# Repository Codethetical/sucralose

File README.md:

# Sucralose

Sucralose is a wireless, 50-key split keyboard built around Kailh PG1316S ultra-low-profile switches.
One reversible PCB serves both halves.

## Rev. 2

Rev. 2 keeps the Rev. 1 key layout and adds:

- **A 7th column on both halves:** four Kailh PG1316M switches sit on a strip outboard of the pinky column.
  Their narrow keycaps, mounted in portrait, minimize the added width.
  The strip is a breakaway section, so you can snap it off and keep a 42-key board.
- **A larger battery cutout:** the bigger opening in the PCB allows a slimmer battery cover.
- **Pads for a slide switch and reset button:** both are on the board edge.

The two halves stacked are now under 13.5 mm tall.

## Hardware

- **Switches:** [Kailh PG1316S](https://www.kailhswitch.com/uploads/15927/files/CPG1316S01D02-data-sheet.pdf),
  21 per half, on a 17 mm pitch to fit their smaller keycaps.
- **7th column:** Kailh PG1316M, 4 per half, on the breakaway strip. The firmware runs with or without it.
- **Controller:** Seeed XIAO nRF52840 Plus, running [ZMK](https://zmk.dev).
- **Display:** [nice!view](https://nicekeyboards.com/nice-view/), soldered flush to keep the stack low.
- **Power:** a LiPo pouch in a corner cutout beside the key field, a JST-PH connector, and a side slide switch.
  An optional side reset button is also supported.
- **PCB:** 1 mm thick, so the full stack stays in ultra-low-profile range.

## Design

- **Layout:** the column splay is inspired by [chalk](https://github.com/maurzo/chalk).
  The 1.5u outer thumb key comes from the [Corne](https://github.com/foostan/crkbd).
- **Reversible:** each half uses the same board, flipped.
  - The XIAO footprint puts a land on both copper layers at every pin.
    Each layer carries the net that pin needs when the module is mounted on that side.
  - The nice!view header can't do that because its pins are plated through-holes.
    Four solder jumpers per side select its pin order instead.
- **Serviceable switches:** the PG1316S contacts sit under the switch body.
  The custom footprint uses plated through-holes so each joint can be reflowed from the underside.

## Custom Footprints

These live in `lib/footprints.pretty/`. The files ending in `_sucralose` were drawn for this board.

- **PG1316S:** a reversible footprint with plated through-holes and locating-pin holes.
  It builds on [mikefive](https://github.com/mikeholscher/zmk-config-mikefive)'s footprints and
  [marbastlib](https://github.com/ebastler/marbastlib)'s.
- **PG1316M:** a reversible footprint with plated through-hole terminals, derived from
  [libmodulo](https://github.com/dennisleexyz/libmodulo)'s.
- **XIAO nRF52840 Plus:** a reversible version of Seeed's official single-sided footprint.
- **nice!view:** a dual-sided header, plus chevron solder jumpers for net selection.
- **Alps SSSS811101 power switch:** front and back versions, checked against
  [ceoloide's footprints](https://github.com/ceoloide/ergogen-footprints).
- **Other parts:** a reversible B3U reset button and SOD-123 diodes.

## Case

`case/out/` has STL files for the partial covers: a battery cover and battery plate, left and right XIAO covers, and a screen cover.
It also has left and right reference DXFs showing the outline, keycap clearances, and M1 screw holes.

## Firmware

This repo is also the [ZMK module](https://zmk.dev/docs/features/modules) for the board: `firmware/` holds the
`sucralose_left` / `sucralose_right` shield. See [`firmware/README.md`](firmware/README.md) for how to build it.

## License

Sucralose is released under the [MIT License](LICENSE).

The key switch layout is the exception. To the extent it is unchanged from [chalk](https://github.com/maurzo/chalk) by maurzo,
that layout stays under chalk's [CC BY-NC-SA 4.0](https://creativecommons.org/licenses/by-nc-sa/4.0/) license.
Third-party files in `reference/` and the footprints derived from upstream libraries also keep their own licenses.

## Credits

- **Corne:** [foostan/crkbd](https://github.com/foostan/crkbd), CC-BY-4.0.
- **Key switch layout:** [maurzo/chalk](https://github.com/maurzo/chalk) by maurzo, CC-BY-NC-SA-4.0.
- **PG1316S footprints:** [mikeholscher/zmk-config-mikefive](https://github.com/mikeholscher/zmk-config-mikefive)
  and [ebastler/marbastlib](https://github.com/ebastler/marbastlib), CERN-OHL-P.
- **PG1316M footprint and 3D model:** [dennisleexyz/libmodulo](https://github.com/dennisleexyz/libmodulo), GPL-3.0.

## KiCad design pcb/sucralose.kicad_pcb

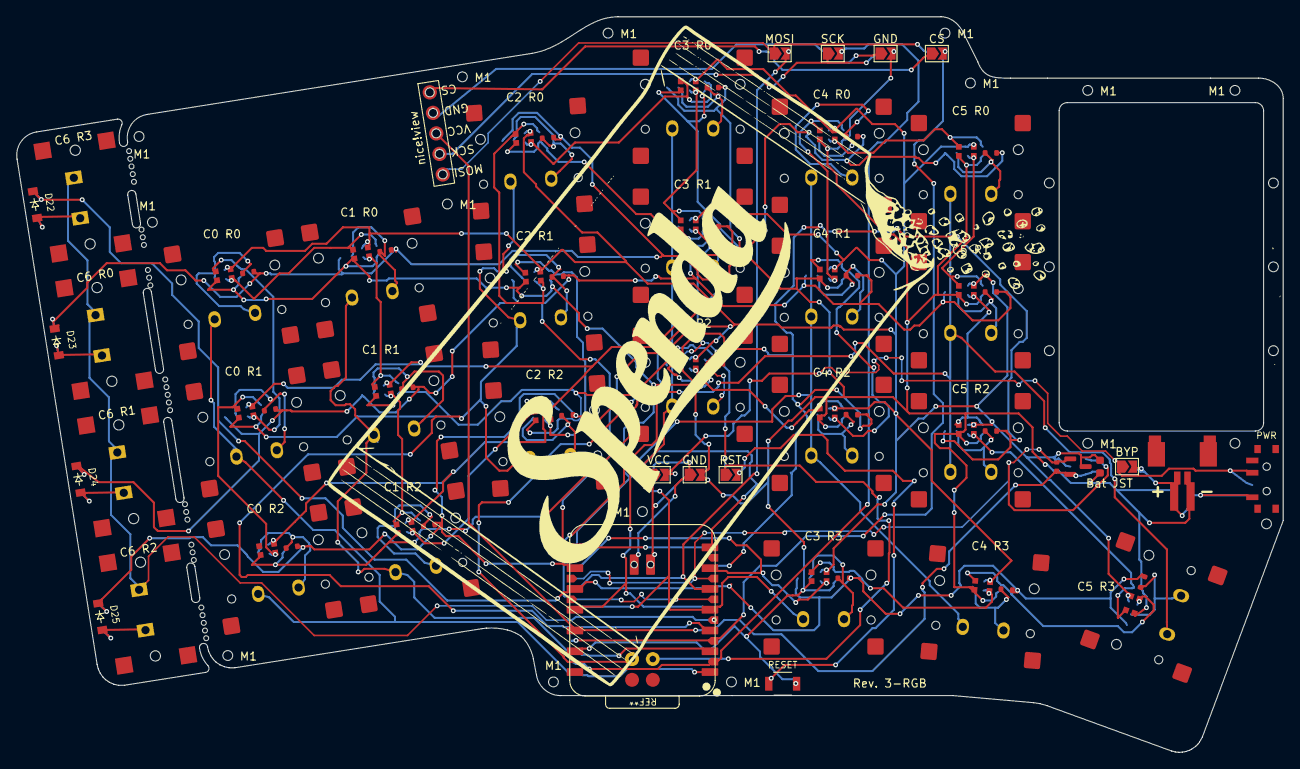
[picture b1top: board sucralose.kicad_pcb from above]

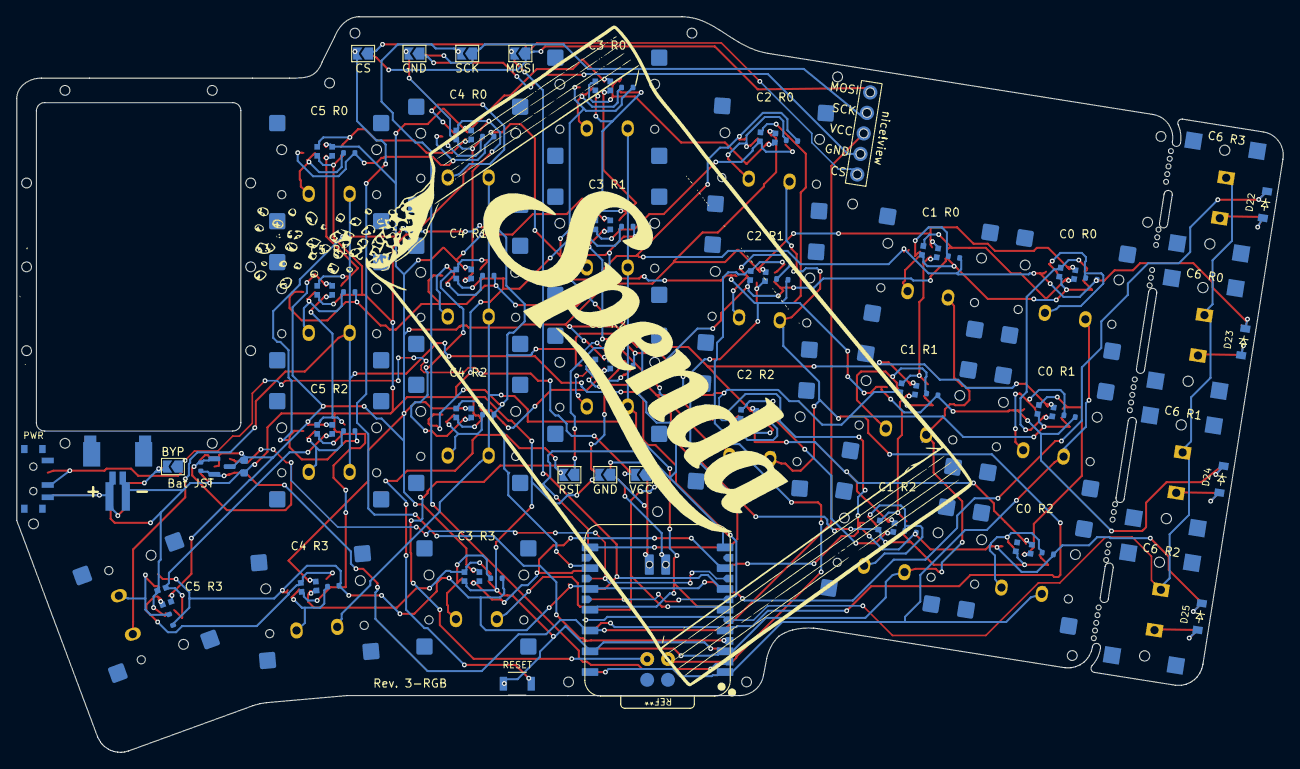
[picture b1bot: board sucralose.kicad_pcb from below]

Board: 2 copper layers, 154.8 x 89.9 mm, 127 parts (14 on the bottom side), 72 nets.

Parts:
BYP: BYP; SolderJumper-2_P1.3mm_Open_TrianglePad1.0x1.5mm
BYP#2: BYP; SolderJumper-2_P1.3mm_Open_TrianglePad1.0x1.5mm
Bat JST: PH S2B / PicoBlade 53261; BAT_JST-PH-S2B_PicoBlade-53261_SideEntry_sucralose
Bat JST#2: PH S2B / PicoBlade 53261; BAT_JST-PH-S2B_PicoBlade-53261_SideEntry_sucralose
C0 R0: CPG1316S01D02_th_reversible_sucralose; SW13
C0 R1: CPG1316S01D02_th_reversible_sucralose; SW5
C0 R2: CPG1316S01D02_th_reversible_sucralose; SW19
C1, C2: 10uF; C_0603_1608Metric
C1 R0: CPG1316S01D02_th_reversible_sucralose; SW16
C1 R1: CPG1316S01D02_th_reversible_sucralose; SW20
C1 R2: CPG1316S01D02_th_reversible_sucralose; SW1
C2 R0: CPG1316S01D02_th_reversible_sucralose; SW3
C2 R1: CPG1316S01D02_th_reversible_sucralose; SW7
C2 R2: CPG1316S01D02_th_reversible_sucralose; SW8
C3 R0: CPG1316S01D02_th_reversible_sucralose; SW14
C3 R1: CPG1316S01D02_th_reversible_sucralose; SW10
C3 R2: CPG1316S01D02_th_reversible_sucralose; SW18
C3 R3: CPG1316S01D02_th_reversible_sucralose; SW4
C4 R0: CPG1316S01D02_th_reversible_sucralose; SW9
C4 R1: CPG1316S01D02_th_reversible_sucralose; SW12
C4 R2: CPG1316S01D02_th_reversible_sucralose; SW2
C4 R3: CPG1316S01D02_th_reversible_sucralose; SW21
C5 R0: CPG1316S01D02_th_reversible_sucralose; SW6
C5 R1: CPG1316S01D02_th_reversible_sucralose; SW11
C5 R2: CPG1316S01D02_th_reversible_sucralose; SW15
C5 R3: CPG1316S01D02_th_reversible_sucralose; SW17
C6 R0, C6 R1, C6 R2, C6 R3: SW_PG1316M_th_reversible_sucralose
CS: CS; SolderJumper-2_P1.3mm_Open_TrianglePad1.0x1.5mm
CS#2: CS; SolderJumper-2_P1.3mm_Open_TrianglePad1.0x1.5mm
D1, D2, D3, D4, D5, D6, D7, D8, D9, D10, D11, D12, D13, D14, D15, D16, D17, D18, D19, D20, D21: 1N4148WT; D_SOD-523_PG1316S_reversible_sucralose
D22, D23, D24, D25: D; diode_sod123_reversible
GND: GND; SolderJumper-2_P1.3mm_Open_TrianglePad1.0x1.5mm
GND#2, GND#3, GND#4: GND; SolderJumper-2_P1.3mm_Open_TrianglePad1.0x1.5mm
L1, L2, L3, L4, L5, L6, L7, L8, L9, L10, L11, L12, L13, L14, L15, L16, L17, L18, L19, L20, L21: WS2812B-2020; LED_WS2812B-2020_PG1316S_reversible_sucralose
M1, M1#2, M1#3, M1#4, M1#5, M1#6, M1#7, M1#8, M1#9, M1#10, M1#11, M1#12, M1#13, M1#14, M1#15, M1#16, M1#17, M1#18, M1#19, M1#20, M1#21, M1#22: MountingHole_1.2mm_M1
MB1, MB2, MB3, MB4, MB5: MouseBite; MouseBite_0.6mm_col7
MOSI: MOSI; SolderJumper-2_P1.3mm_Open_TrianglePad1.0x1.5mm
MOSI#2: MOSI; SolderJumper-2_P1.3mm_Open_TrianglePad1.0x1.5mm
PWR: SSSS811101; SW_Slide_SSSS811101_Side_F_sucralose
PWR#2: SSSS811101; SW_Slide_SSSS811101_Side_B_sucralose
Q1, Q2: AO3401A; SOT-23
R1, R2: 100k; R_0402_1005Metric
RESET: B3U-1000P; SW_Tactile_B3U-1000P_Reversible_sucralose
RST: RST; SolderJumper-2_P1.3mm_Open_TrianglePad1.0x1.5mm
RST#2: RST; SolderJumper-2_P1.3mm_Open_TrianglePad1.0x1.5mm
SCK: SCK; SolderJumper-2_P1.3mm_Open_TrianglePad1.0x1.5mm
SCK#2: SCK; SolderJumper-2_P1.3mm_Open_TrianglePad1.0x1.5mm
VCC: VCC; SolderJumper-2_P1.3mm_Open_TrianglePad1.0x1.5mm
VCC#2: VCC; SolderJumper-2_P1.3mm_Open_TrianglePad1.0x1.5mm
display*: nice!view; nice_view
display*#2: nice!view; nice_view

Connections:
BATH_A: GND#3.1, VCC.1
BATH_B: GND#2.1, VCC#2.1
BAT_P: BYP.1, BYP#2.1, PWR.2, PWR#2.2, VCC.2, VCC#2.2
BAT_RAW: BYP.2, BYP#2.2, Bat JST.2, Bat JST#2.2, PWR.1, PWR#2.3
COL0: C0 R0.1, C0 R1.1, C0 R2.1
COL1: C1 R0.1, C1 R1.1, C1 R2.1
COL2: C2 R0.1, C2 R1.1, C2 R2.1
COL3: C3 R0.1, C3 R1.1, C3 R2.1, C3 R3.1
COL4: C4 R0.1, C4 R1.1, C4 R2.1, C4 R3.1
COL5: C5 R0.1, C5 R1.1, C5 R2.1, C5 R3.1
COL6: C6 R0.1, C6 R1.1, C6 R2.1, C6 R3.1
CS: CS.2, CS#2.2
DISP_H1: CS#2.1, MOSI.1, display*.1, display*#2.5
DISP_H2: GND#4.1, SCK.1, display*.2, display*#2.4
DISP_H4: GND.1, SCK#2.1, display*.4, display*#2.2
DISP_H5: CS.1, MOSI#2.1, display*.5, display*#2.1
GND: Bat JST.1, Bat JST#2.1, C1.2, C2.2, GND.2, GND#2.2, GND#3.2, GND#4.2, L1.2, L2.2, L3.2, L4.2, L5.2, L6.2, L7.2, L8.2, L9.2, L10.2, L11.2, L12.2, L13.2, L14.2, L15.2, L16.2, L17.2, L18.2, L19.2, L20.2, L21.2, RESET.2
LD1: L1.1, L2.3
LD2: L2.1, L3.3
LD3: L3.1, L4.3
LD4: L4.1, L5.3
LD5: L5.1, L6.3
LD6: L6.1, L7.3
LD7: L7.1, L8.3
LD8: L8.1, L9.3
LD9: L9.1, L10.3
LD10: L10.1, L11.3
LD11: L11.1, L12.3
LD12: L12.1, L13.3
LD13: L13.1, L14.3
LD14: L14.1, L15.3
LD15: L15.1, L16.3
LD16: L16.1, L17.3
LD17: L17.1, L18.3
LD18: L18.1, L19.3
LD19: L19.1, L20.3
LD20: L20.1, L21.3
LED_EN: Q1.1, Q2.1, R1.1, R2.1
MOSI: MOSI.2, MOSI#2.2
ROW0: D3.1, D6.1, D9.1, D13.1, D14.1, D16.1, D23.1
ROW1: D5.1, D7.1, D10.1, D11.1, D12.1, D20.1, D24.1
ROW2: D1.1, D2.1, D8.1, D15.1, D18.1, D19.1, D25.1
ROW3: D4.1, D17.1, D21.1, D22.1
RST: RESET.1, RST.2, RST#2.2
SCK: SCK.2, SCK#2.2
VCC: Q1.2, Q2.2, R1.2, R2.2, display*.3, display*#2.3
VLED: C1.1, C2.1, L1.4, L2.4, L3.4, L4.4, L5.4, L6.4, L7.4, L8.4, L9.4, L10.4, L11.4, L12.4, L13.4, L14.4, L15.4, L16.4, L17.4, L18.4, L19.4, L20.4, L21.4, Q1.3, Q2.3
far_thumb: C5 R3.2, D17.2
home_thumb: C4 R3.2, D21.2
index_bottom: C4 R2.2, D2.2
index_home: C4 R1.2, D12.2
index_top: C4 R0.2, D9.2
inner_bottom: C5 R2.2, D15.2
inner_home: C5 R1.2, D11.2
inner_top: C5 R0.2, D6.2
middle_bottom: C3 R2.2, D18.2
middle_home: C3 R1.2, D10.2
middle_top: C3 R0.2, D14.2
near_thumb: C3 R3.2, D4.2
outer_bottom: C0 R2.2, D19.2
outer_home: C0 R1.2, D5.2
outer_top: C0 R0.2, D13.2
pinky7_bottom: C6 R2.2, D25.2
pinky7_extra: C6 R3.2, D22.2
pinky7_home: C6 R1.2, D24.2
pinky7_top: C6 R0.2, D23.2
pinky_bottom: C1 R2.2, D1.2
pinky_home: C1 R1.2, D20.2
pinky_top: C1 R0.2, D16.2
ring_bottom: C2 R2.2, D8.2
ring_home: C2 R1.2, D7.2
ring_top: C2 R0.2, D3.2

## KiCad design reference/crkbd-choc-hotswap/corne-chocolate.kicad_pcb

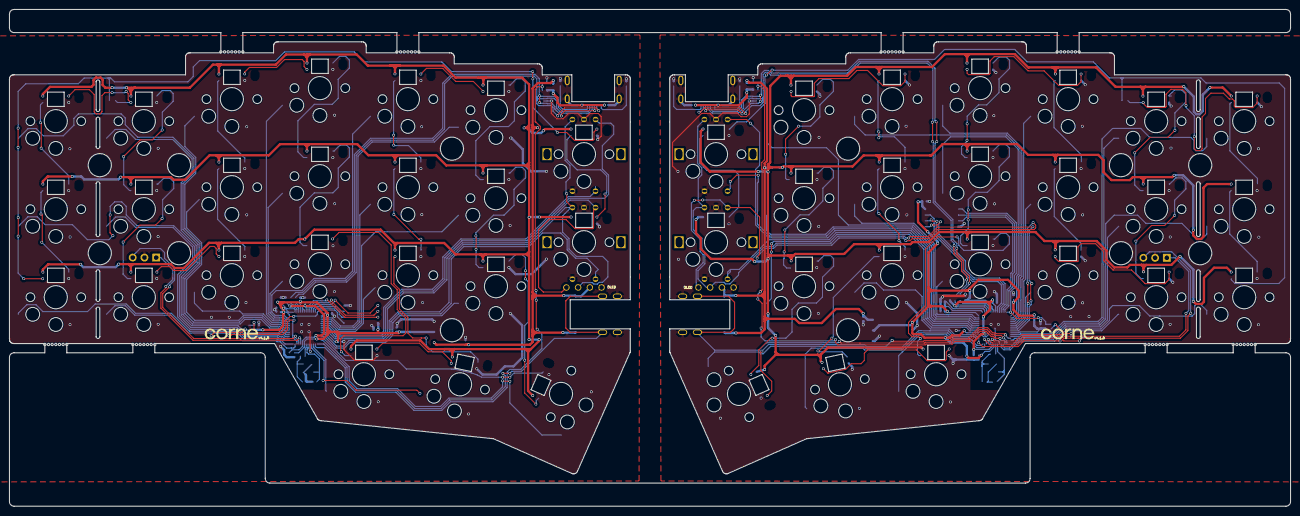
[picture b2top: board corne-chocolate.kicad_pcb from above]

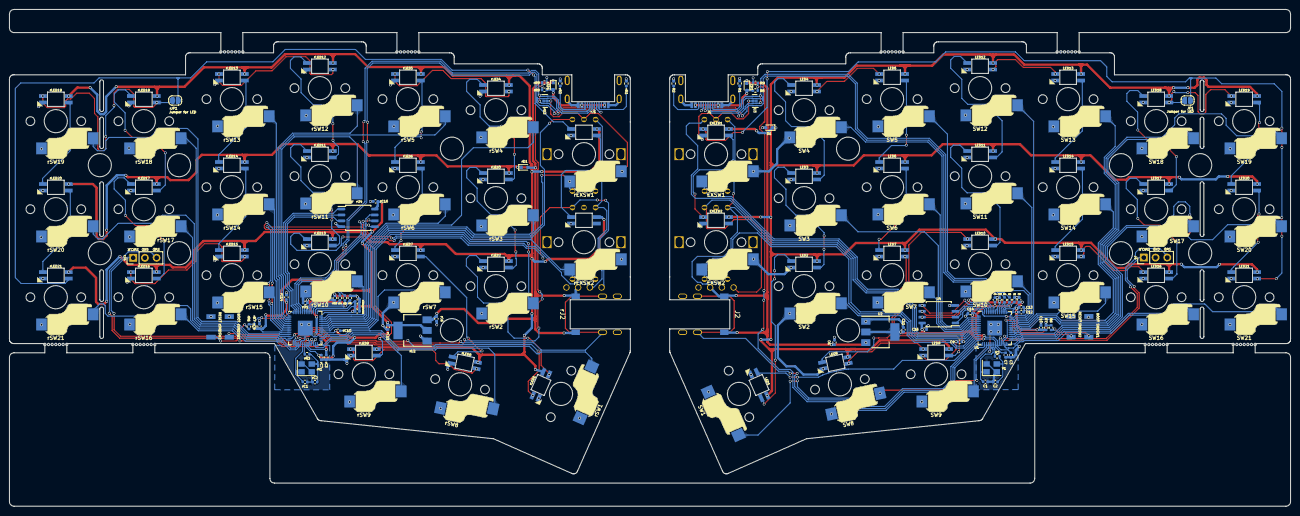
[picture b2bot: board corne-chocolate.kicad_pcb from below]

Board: 2 copper layers, 277.2 x 107.5 mm, 178 parts (168 on the bottom side), 152 nets.

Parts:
BT1, BT2, BT3, BT4: Breakaway Tabs; Breakaway_Tabs
C1, C2: 27p; C_0402_1005Metric
C3, C4, C7, C9, C10, C12, C13, C14, C15: 100n; C_0402_1005Metric
C5, C8, C16: 1u; C_0402_1005Metric
C6, C11: 10u; C_0402_1005Metric
D1: 1N4148WT; D_SOD-523
EXLED1, EXLED2: YS-SK6812MINI-E
EXSW1, EXSW2: RotaryEncoder_Switch; keyswitch_choc12_hotswap_1u_rotary_encoder_ec12
J1: TYPE-C-31-M-13C
J2: TRS; PJ-398A-5A_PJ-399B-6A
J3: Conn_01x04; OLED
J4: Conn_01x03; PinHeader_1x03_P2.54mm_Vertical
JP1: SolderJumper_2_Bridged; SolderJumper-2_P1.3mm_Open_RoundedPad1.0x1.5mm
LED1, LED2, LED3, LED4, LED5, LED6, LED7, LED8, LED9, LED10, LED11, LED12, LED13, LED14, LED15, LED16, LED17, LED18, LED19, LED20, LED21: YS-SK6812MINI-E
R1, R2: 5.1k; R_0402_1005Metric
R3, R6: 1k; R_0402_1005Metric
R4, R5: 27; R_0402_1005Metric
R7: 10k; R_0402_1005Metric
R8: 5.6k; R_0402_1005Metric
R9: 10K; R_0402_1005Metric
SMDSW1, SMDSW2: TS-1088R-02026
SW1: SW_Push; keyswitch_choc12_hotswap_1.5u
SW2, SW3, SW4, SW5, SW6, SW7, SW8, SW9, SW10, SW11, SW12, SW13, SW14, SW15, SW16, SW17, SW18, SW19, SW20, SW21: SW_Push; keyswitch_choc12_hotswap_1u
U1: RP2040; QFN-56-1EP_7x7mm_P0.4mm_EP3.2x3.2mm
U2: NCP1117LPST33T3G; SOT-223-3_TabPin2
U3: TPD4E05U06DQAR; USON-10_2.5x1.0mm_P0.5mm
U4: W25Q128JVSIQ; SOIC-8_5.23x5.23mm_P1.27mm
Y1: 12MHz 18pF; Crystal_SMD_3225-4Pin_3.2x2.5mm
ZD1: RB521S30T1G; D_SOD-523
rBT1, rBT2, rBT3, rBT4: Breakaway Tabs; Breakaway_Tabs
rC1, rC2: 27p; C_0402_1005Metric
rC3, rC4, rC7, rC9, rC10, rC12, rC13, rC14, rC15: 100n; C_0402_1005Metric
rC5, rC8, rC16: 1u; C_0402_1005Metric
rC6, rC11: 10u; C_0402_1005Metric
rD1: 1N4148WT; D_SOD-523
rEXLED1, rEXLED2: YS-SK6812MINI-E
rEXSW1, rEXSW2: RotaryEncoder_Switch; keyswitch_choc12_hotswap_1u_rotary_encoder_ec12
rJ1: TYPE-C-31-M-13C
rJ2: TRS; PJ-398A-5A_PJ-399B-6A
rJ3: Conn_01x04; OLED
rJ4: Conn_01x03; PinHeader_1x03_P2.54mm_Vertical
rJP1: SolderJumper_2_Bridged; SolderJumper-2_P1.3mm_Open_RoundedPad1.0x1.5mm
rLED1, rLED2, rLED3, rLED4, rLED5, rLED6, rLED7, rLED8, rLED9, rLED10, rLED11, rLED12, rLED13, rLED14, rLED15, rLED16, rLED17, rLED18, rLED19, rLED20, rLED21: YS-SK6812MINI-E
rR1, rR2: 5.1k; R_0402_1005Metric
rR3, rR6: 1k; R_0402_1005Metric
rR4, rR5: 27; R_0402_1005Metric
rR7: 10k; R_0402_1005Metric
rR8: 5.6k; R_0402_1005Metric
rR9: 10K; R_0402_1005Metric
rSMDSW1, rSMDSW2: TS-1088R-02026
rSW1: SW_Push; keyswitch_choc12_hotswap_1.5u
rSW2, rSW3, rSW4, rSW5, rSW6, rSW7, rSW8, rSW9, rSW10, rSW11, rSW12, rSW13, rSW14, rSW15, rSW16, rSW17, rSW18, rSW19, rSW20, rSW21: SW_Push; keyswitch_choc12_hotswap_1u
rU1: RP2040; QFN-56-1EP_7x7mm_P0.4mm_EP3.2x3.2mm
rU2: NCP1117LPST33T3G; SOT-223-3_TabPin2
rU3: TPD4E05U06DQAR; USON-10_2.5x1.0mm_P0.5mm
rU4: W25Q128JVSIQ; SOIC-8_5.23x5.23mm_P1.27mm
rY1: 12MHz 18pF; Crystal_SMD_3225-4Pin_3.2x2.5mm
rZD1: RB521S30T1G; D_SOD-523

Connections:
+1V1: C3.1, C4.1, C5.1, U1.23 (DVDD), U1.45 (VREG_VOUT), U1.50 (DVDD)
+1V1R: rC3.1, rC4.1, rC5.1, rU1.23 (DVDD), rU1.45 (VREG_VOUT), rU1.50 (DVDD)
+3V3: C7.1, C8.1, C9.1, C10.1, C11.1, C12.1, C13.1, C14.1, C15.1, C16.1, R7.2, U1.1 (IOVDD), U1.10 (IOVDD), U1.22 (IOVDD), U1.32 (GPIO21), U1.33 (IOVDD), U1.42 (IOVDD), U1.43 (ADC_AVDD), U1.44 (VREG_IN), U1.48 (USB_VDD), U1.49 (IOVDD), U2.2 (VO), U4.8 (VCC)
+3V3R: rC7.1, rC8.1, rC9.1, rC10.1, rC11.1, rC12.1, rC13.1, rC14.1, rC15.1, rC16.1, rR7.2, rU1.1 (IOVDD), rU1.10 (IOVDD), rU1.22 (IOVDD), rU1.33 (IOVDD), rU1.42 (IOVDD), rU1.43 (ADC_AVDD), rU1.44 (VREG_IN), rU1.48 (USB_VDD), rU1.49 (IOVDD), rU2.2 (VO), rU4.8 (VCC)
+5V: C6.1, D1.2 (A), J2.T, J3.3, U2.3 (VI), ZD1.1 (K)
+5VR: rC6.1, rD1.2 (A), rJ2.T, rJ3.3, rU2.3 (VI), rZD1.1 (K)
/left/D+: J1.A6 (D+), J1.B6 (D+), R4.1, U3.1 (D1+), U3.4 (D2+), U3.7 (NC), U3.10 (NC)
/left/D-: J1.A7 (D-), J1.B7 (D-), R5.2, U3.2 (D1-), U3.5 (D2-), U3.6 (NC), U3.9 (NC)
/left/KEY1: SW1.1, U1.14 (GPIO11)
/left/KEY2: SW2.1, U1.12 (GPIO9)
/left/KEY3: SW3.1, U1.4 (GPIO2)
/left/KEY4: SW4.1, U1.2 (GPIO0)
/left/KEY5: SW5.1, U1.41 (GPIO29_ADC3)
/left/KEY6: SW6.1, U1.3 (GPIO1)
/left/KEY7: SW7.1, U1.5 (GPIO3)
/left/KEY8: SW8.1, U1.18 (GPIO15)
/left/KEY9: SW9.1, U1.17 (GPIO14)
/left/KEY10: SW10.1, U1.40 (GPIO28_ADC2)
/left/KEY11: SW11.1, U1.39 (GPIO27_ADC1)
/left/KEY12: SW12.1, U1.38 (GPIO26_ADC0)
/left/KEY13: SW13.1, U1.35 (GPIO23)
/left/KEY14: SW14.1, U1.36 (GPIO24)
/left/KEY15: SW15.1, U1.37 (GPIO25)
/left/KEY16: SW16.1, U1.27 (GPIO16)
/left/KEY17: SW17.1, U1.29 (GPIO18)
/left/KEY18: SW18.1, U1.31 (GPIO20)
/left/KEY19: SW19.1, U1.34 (GPIO22)
/left/KEY20: SW20.1, U1.30 (GPIO19)
/left/KEY21: SW21.1, U1.28 (GPIO17)
/left/KEYEX1: EXSW1.S2, U1.6 (GPIO4)
/left/KEYEX2: EXSW2.S2, U1.11 (GPIO8)
/left/LED: LED1.4 (DIN), U1.13 (GPIO10)
/left/QSPI_SCLK: U1.52 (QSPI_SCLK), U4.6 (CLK)
/left/QSPI_SD0: U1.53 (QSPI_SD0), U4.5 (DI(IO0))
/left/QSPI_SD1: U1.55 (QSPI_SD1), U4.2 (DO(IO1))
/left/QSPI_SD2: U1.54 (QSPI_SD2), U4.3 (IO2)
/left/QSPI_SD3: U1.51 (QSPI_SD3), U4.7 (IO3)
/left/QSPI_SS: R6.1, R7.1, U1.56 (QSPI_SS), U4.1 (~CS)
/left/RE0A: EXSW1.A, U1.7 (GPIO5)
/left/RE1A: EXSW2.A, J3.1, U1.8 (GPIO6)
/left/REB: EXSW1.B, EXSW2.B, J3.2, U1.9 (GPIO7)
/left/SWCLK: J4.1, U1.24 (SWCLK)
/left/SWD: J4.3, U1.25 (SWD)
/left/TX: J2.R, U1.15 (GPIO12)
/left/USB_VBUS_PIN: R8.2, R9.1, U1.16 (GPIO13)
/right/D+: rJ1.A6 (D+), rJ1.B6 (D+), rR4.1, rU3.1 (D1+), rU3.4 (D2+), rU3.7 (NC), rU3.10 (NC)
/right/D-: rJ1.A7 (D-), rJ1.B7 (D-), rR5.2, rU3.2 (D1-), rU3.5 (D2-), rU3.6 (NC), rU3.9 (NC)
/right/KEY1: rSW1.1, rU1.30 (GPIO19)
/right/KEY2: rSW2.1, rU1.34 (GPIO22)
/right/KEY3: rSW3.1, rU1.38 (GPIO26_ADC0)
/right/KEY4: rSW4.1, rU1.39 (GPIO27_ADC1)
/right/KEY5: rSW5.1, rU1.3 (GPIO1)
/right/KEY6: rSW6.1, rU1.40 (GPIO28_ADC2)
/right/KEY7: rSW7.1, rU1.31 (GPIO20)
/right/KEY8: rSW8.1, rU1.28 (GPIO17)
/right/KEY9: rSW9.1, rU1.27 (GPIO16)
/right/KEY10: rSW10.1, rU1.41 (GPIO29_ADC3)
/right/KEY11: rSW11.1, rU1.2 (GPIO0)
/right/KEY12: rSW12.1, rU1.4 (GPIO2)
/right/KEY13: rSW13.1, rU1.5 (GPIO3)
/right/KEY14: rSW14.1, rU1.6 (GPIO4)
/right/KEY15: rSW15.1, rU1.7 (GPIO5)
/right/KEY16: rSW16.1, rU1.29 (GPIO18)
/right/KEY17: rSW17.1, rU1.17 (GPIO14)
/right/KEY18: rSW18.1, rU1.12 (GPIO9)
/right/KEY19: rSW19.1, rU1.11 (GPIO8)
/right/KEY20: rSW20.1, rU1.14 (GPIO11)
/right/KEY21: rSW21.1, rU1.18 (GPIO15)
/right/KEYEX1: rEXSW1.S2, rU1.37 (GPIO25)
/right/KEYEX2: rEXSW2.S2, rU1.35 (GPIO23)
/right/LED: rLED1.4 (DIN), rU1.13 (GPIO10)
/right/QSPI_SCLK: rU1.52 (QSPI_SCLK), rU4.6 (CLK)
/right/QSPI_SD0: rU1.53 (QSPI_SD0), rU4.5 (DI(IO0))
/right/QSPI_SD1: rU1.55 (QSPI_SD1), rU4.2 (DO(IO1))
/right/QSPI_SD2: rU1.54 (QSPI_SD2), rU4.3 (IO2)
/right/QSPI_SD3: rU1.51 (QSPI_SD3), rU4.7 (IO3)
/right/QSPI_SS: rR6.1, rR7.1, rU1.56 (QSPI_SS), rU4.1 (~CS)
/right/RE0A: rEXSW1.A, rU1.36 (GPIO24)
/right/RE1A: rEXSW2.A, rJ3.1, rU1.8 (GPIO6)
/right/REB: rEXSW1.B, rEXSW2.B, rJ3.2, rU1.9 (GPIO7)
/right/SWCLK: rJ4.1, rU1.24 (SWCLK)
/right/SWD: rJ4.3, rU1.25 (SWD)
/right/TX: rJ2.R, rU1.15 (GPIO12)
/right/USB_VBUS_PIN: rR8.2, rR9.1, rU1.16 (GPIO13)
GND: C1.2, C2.2, C3.2, C4.2, C5.2, C6.2, C7.2, C8.2, C9.2, C10.2, C11.2, C12.2, C13.2, C14.2, C15.2, C16.2, EXLED1.3 (VSS), EXLED2.3 (VSS), EXSW1.C, EXSW1.S1, EXSW2.C, EXSW2.S1, J1.A1 (GND), J1.A12 (GND), J1.B1 (GND), J1.B12 (GND), J1.S1 (SHIELD), J2.S, J3.4, J4.2, LED1.3 (VSS), LED2.3 (VSS), LED3.3 (VSS), LED4.3 (VSS), LED5.3 (VSS), LED6.3 (VSS), LED7.3 (VSS), LED8.3 (VSS), LED9.3 (VSS), LED10.3 (VSS), LED11.3 (VSS), LED12.3 (VSS), LED13.3 (VSS), LED14.3 (VSS), LED15.3 (VSS), LED16.3 (VSS), LED17.3 (VSS), LED18.3 (VSS), LED19.3 (VSS), LED20.3 (VSS), LED21.3 (VSS), R1.1, R2.1, R9.2, SMDSW1.1, SMDSW2.1, SW1.2, SW2.2, SW3.2, SW4.2, SW5.2, SW6.2, SW7.2, SW8.2, SW9.2, SW10.2, SW11.2, SW12.2, SW13.2, SW14.2, SW15.2, SW16.2, SW17.2, SW18.2, SW19.2, SW20.2, SW21.2, U1.19 (TESTEN), U1.57 (GND), U2.1 (GND), U3.3 (GND), U3.8 (GND), U4.4 (GND), Y1.2, Y1.4
GNDR: rC1.2, rC2.2, rC3.2, rC4.2, rC5.2, rC6.2, rC7.2, rC8.2, rC9.2, rC10.2, rC11.2, rC12.2, rC13.2, rC14.2, rC15.2, rC16.2, rEXLED1.3 (VSS), rEXLED2.3 (VSS), rEXSW1.C, rEXSW1.S1, rEXSW2.C, rEXSW2.S1, rJ1.A1 (GND), rJ1.A12 (GND), rJ1.B1 (GND), rJ1.B12 (GND), rJ1.S1 (SHIELD), rJ2.S, rJ3.4, rJ4.2, rLED1.3 (VSS), rLED2.3 (VSS), rLED3.3 (VSS), rLED4.3 (VSS), rLED5.3 (VSS), rLED6.3 (VSS), rLED7.3 (VSS), rLED8.3 (VSS), rLED9.3 (VSS), rLED10.3 (VSS), rLED11.3 (VSS), rLED12.3 (VSS), rLED13.3 (VSS), rLED14.3 (VSS), rLED15.3 (VSS), rLED16.3 (VSS), rLED17.3 (VSS), rLED18.3 (VSS), rLED19.3 (VSS), rLED20.3 (VSS), rLED21.3 (VSS), rR1.1, rR2.1, rR9.2, rSMDSW1.1, rSMDSW2.1, rSW1.2, rSW2.2, rSW3.2, rSW4.2, rSW5.2, rSW6.2, rSW7.2, rSW8.2, rSW9.2, rSW10.2, rSW11.2, rSW12.2, rSW13.2, rSW14.2, rSW15.2, rSW16.2, rSW17.2, rSW18.2, rSW19.2, rSW20.2, rSW21.2, rU1.19 (TESTEN), rU1.32 (GPIO21), rU1.57 (GND), rU2.1 (GND), rU3.3 (GND), rU3.8 (GND), rU4.4 (GND), rY1.2, rY1.4
unnamed: C2.1, R3.1, Y1.3
unnamed: D1.1 (K), EXLED1.1 (VDD), EXLED2.1 (VDD), LED1.1 (VDD), LED2.1 (VDD), LED3.1 (VDD), LED4.1 (VDD), LED5.1 (VDD), LED6.1 (VDD), LED7.1 (VDD), LED8.1 (VDD), LED9.1 (VDD), LED10.1 (VDD), LED11.1 (VDD), LED12.1 (VDD), LED13.1 (VDD), LED14.1 (VDD), LED15.1 (VDD), LED16.1 (VDD), LED17.1 (VDD), LED18.1 (VDD), LED19.1 (VDD), LED20.1 (VDD), LED21.1 (VDD)
unnamed: EXLED1.4 (DIN), JP1.2 (B), LED21.2 (DOUT)
unnamed: EXLED1.2 (DOUT), EXLED2.4 (DIN)
unnamed: J1.A5 (CC1), R1.2
unnamed: J1.B5 (CC2), R2.2
unnamed: JP1.1 (A), LED18.2 (DOUT), LED19.4 (DIN)
unnamed: LED1.2 (DOUT), LED2.4 (DIN)
unnamed: LED2.2 (DOUT), LED3.4 (DIN)
unnamed: LED3.2 (DOUT), LED4.4 (DIN)
unnamed: LED4.2 (DOUT), LED5.4 (DIN)
unnamed: LED5.2 (DOUT), LED6.4 (DIN)
unnamed: LED6.2 (DOUT), LED7.4 (DIN)
unnamed: LED7.2 (DOUT), LED8.4 (DIN)
unnamed: LED8.2 (DOUT), LED9.4 (DIN)
unnamed: LED9.2 (DOUT), LED10.4 (DIN)
unnamed: LED10.2 (DOUT), LED11.4 (DIN)
unnamed: LED11.2 (DOUT), LED12.4 (DIN)
unnamed: LED12.2 (DOUT), LED13.4 (DIN)
unnamed: LED13.2 (DOUT), LED14.4 (DIN)
unnamed: LED14.2 (DOUT), LED15.4 (DIN)
unnamed: LED15.2 (DOUT), LED16.4 (DIN)
unnamed: LED16.2 (DOUT), LED17.4 (DIN)
unnamed: LED17.2 (DOUT), LED18.4 (DIN)
unnamed: LED19.2 (DOUT), LED20.4 (DIN)
unnamed: LED20.2 (DOUT), LED21.4 (DIN)
unnamed: R6.2, SMDSW1.2
unnamed: SMDSW2.2, U1.26 (RUN)
unnamed: R5.1, U1.46 (USB_DM)
unnamed: R4.2, U1.47 (USB_DP)
unnamed: C1.1, U1.20 (XIN), Y1.1
unnamed: R3.2, U1.21 (XOUT)
unnamed: rC2.1, rR3.1, rY1.3
unnamed: rD1.1 (K), rEXLED1.1 (VDD), rEXLED2.1 (VDD), rLED1.1 (VDD), rLED2.1 (VDD), rLED3.1 (VDD), rLED4.1 (VDD), rLED5.1 (VDD), rLED6.1 (VDD), rLED7.1 (VDD), rLED8.1 (VDD), rLED9.1 (VDD), rLED10.1 (VDD), rLED11.1 (VDD), rLED12.1 (VDD), rLED13.1 (VDD), rLED14.1 (VDD), rLED15.1 (VDD), rLED16.1 (VDD), rLED17.1 (VDD), rLED18.1 (VDD), rLED19.1 (VDD), rLED20.1 (VDD), rLED21.1 (VDD)
unnamed: rEXLED1.4 (DIN), rJP1.2 (B), rLED21.2 (DOUT)
unnamed: rEXLED1.2 (DOUT), rEXLED2.4 (DIN)
unnamed: rJ1.A5 (CC1), rR1.2
unnamed: rJ1.B5 (CC2), rR2.2
unnamed: rJP1.1 (A), rLED18.2 (DOUT), rLED19.4 (DIN)
unnamed: rLED1.2 (DOUT), rLED2.4 (DIN)
unnamed: rLED2.2 (DOUT), rLED3.4 (DIN)
unnamed: rLED3.2 (DOUT), rLED4.4 (DIN)
unnamed: rLED4.2 (DOUT), rLED5.4 (DIN)
unnamed: rLED5.2 (DOUT), rLED6.4 (DIN)
unnamed: rLED6.2 (DOUT), rLED7.4 (DIN)
unnamed: rLED7.2 (DOUT), rLED8.4 (DIN)
unnamed: rLED8.2 (DOUT), rLED9.4 (DIN)
unnamed: rLED9.2 (DOUT), rLED10.4 (DIN)
unnamed: rLED10.2 (DOUT), rLED11.4 (DIN)
unnamed: rLED11.2 (DOUT), rLED12.4 (DIN)
unnamed: rLED12.2 (DOUT), rLED13.4 (DIN)
unnamed: rLED13.2 (DOUT), rLED14.4 (DIN)
unnamed: rLED14.2 (DOUT), rLED15.4 (DIN)
unnamed: rLED15.2 (DOUT), rLED16.4 (DIN)
unnamed: rLED16.2 (DOUT), rLED17.4 (DIN)
unnamed: rLED17.2 (DOUT), rLED18.4 (DIN)
unnamed: rLED19.2 (DOUT), rLED20.4 (DIN)
unnamed: rLED20.2 (DOUT), rLED21.4 (DIN)
unnamed: rR6.2, rSMDSW1.2
unnamed: rSMDSW2.2, rU1.26 (RUN)
unnamed: rR5.1, rU1.46 (USB_DM)
unnamed: rR4.2, rU1.47 (USB_DP)
unnamed: rC1.1, rU1.20 (XIN), rY1.1
unnamed: rR3.2, rU1.21 (XOUT)
VBUS: J1.A4 (VBUS), J1.A9 (VBUS), J1.B4 (VBUS), J1.B9 (VBUS), R8.1, ZD1.2 (A)
VBUSR: rJ1.A4 (VBUS), rJ1.A9 (VBUS), rJ1.B4 (VBUS), rJ1.B9 (VBUS), rR8.1, rZD1.2 (A)

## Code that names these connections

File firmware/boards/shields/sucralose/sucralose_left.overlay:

/*
 * Copyright (c) 2026 The ZMK Contributors
 *
 * SPDX-License-Identifier: MIT
 */

#include "sucralose.dtsi"

/*
 * XIAO on the front face: COL6 (breakaway strip) is leftmost, then COL0
 * (pinky). COL6 is D13, a Plus-only pad the xiao_d connector does not map,
 * so it is given as a raw port.
 */
&kscan0 {
    col-gpios
        = <&gpio1 1 GPIO_ACTIVE_HIGH>    /* COL6 */
        , <&xiao_d 0 GPIO_ACTIVE_HIGH>   /* COL0 */
        , <&xiao_d 1 GPIO_ACTIVE_HIGH>   /* COL1 */
        , <&xiao_d 2 GPIO_ACTIVE_HIGH>   /* COL2 */
        , <&xiao_d 3 GPIO_ACTIVE_HIGH>   /* COL3 */
        , <&xiao_d 10 GPIO_ACTIVE_HIGH>  /* COL4 */
        , <&gpio0 9 GPIO_ACTIVE_HIGH>   /* COL5  D14 P0.09 (NFC pin, see uicr) */
        ;
};

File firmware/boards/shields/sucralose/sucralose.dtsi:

/*
 * Copyright (c) 2026 The ZMK Contributors
 *
 * SPDX-License-Identifier: MIT
 */

#include <dt-bindings/zmk/matrix_transform.h>

#include "sucralose-layouts.dtsi"

/ {
    chosen {
        zmk,kscan = &kscan0;
        zmk,physical-layout = &sucralose_7col_layout;
    };

    default_transform: keymap_transform_0 {
        compatible = "zmk,matrix-transform";
        columns = <14>;
        rows = <4>;
// | C6R3 |                                                                                                       | C6R3 |
// | C6R0 | C0R0 | C1R0 | C2R0 | C3R0 | C4R0 | C5R0 |   | C5R0 | C4R0 | C3R0 | C2R0 | C1R0 | C0R0 | C6R0 |
// | C6R1 | C0R1 | C1R1 | C2R1 | C3R1 | C4R1 | C5R1 |   | C5R1 | C4R1 | C3R1 | C2R1 | C1R1 | C0R1 | C6R1 |
// | C6R2 | C0R2 | C1R2 | C2R2 | C3R2 | C4R2 | C5R2 |   | C5R2 | C4R2 | C3R2 | C2R2 | C1R2 | C0R2 | C6R2 |
//                             | C3R3 | C4R3 | C5R3 |   | C5R3 | C4R3 | C3R3 |
// Silkscreen labels. COL0 is the pinky column on both halves; COL6 is the
// breakaway strip outboard of it, and C6R3 sits above C6R0. C5R3 is the 1.5u
// thumb nearest the split.
        map = <
RC(3,0)                                                                                               RC(3,13)
RC(0,0) RC(0,1) RC(0,2) RC(0,3) RC(0,4) RC(0,5) RC(0,6)  RC(0,7) RC(0,8) RC(0,9) RC(0,10) RC(0,11) RC(0,12) RC(0,13)
RC(1,0) RC(1,1) RC(1,2) RC(1,3) RC(1,4) RC(1,5) RC(1,6)  RC(1,7) RC(1,8) RC(1,9) RC(1,10) RC(1,11) RC(1,12) RC(1,13)
RC(2,0) RC(2,1) RC(2,2) RC(2,3) RC(2,4) RC(2,5) RC(2,6)  RC(2,7) RC(2,8) RC(2,9) RC(2,10) RC(2,11) RC(2,12) RC(2,13)
                                RC(3,4) RC(3,5) RC(3,6)  RC(3,7) RC(3,8) RC(3,9)
        >;
    };

    six_col_transform: keymap_transform_1 {
        compatible = "zmk,matrix-transform";
        columns = <14>;
        rows = <4>;
// default_transform without COL6.
        map = <
RC(0,1) RC(0,2) RC(0,3) RC(0,4) RC(0,5) RC(0,6)  RC(0,7) RC(0,8) RC(0,9) RC(0,10) RC(0,11) RC(0,12)
RC(1,1) RC(1,2) RC(1,3) RC(1,4) RC(1,5) RC(1,6)  RC(1,7) RC(1,8) RC(1,9) RC(1,10) RC(1,11) RC(1,12)
RC(2,1) RC(2,2) RC(2,3) RC(2,4) RC(2,5) RC(2,6)  RC(2,7) RC(2,8) RC(2,9) RC(2,10) RC(2,11) RC(2,12)
                        RC(3,4) RC(3,5) RC(3,6)  RC(3,7) RC(3,8) RC(3,9)
        >;
    };

    /*
     * One reversible PCB serves both halves and both XIAO lands carry the
     * same nets, so the pins are identical; only the column order differs
     * (see sucralose_left/right.overlay). Pin choices: docs/PINOUT.md.
     * COL6 is scanned whether or not the strip is attached; a snapped board
     * just never sees those keys.
     */
    kscan0: kscan {
        compatible = "zmk,kscan-gpio-matrix";
        wakeup-source;

        diode-direction = "col2row";
        row-gpios
            = <&xiao_d 6 (GPIO_ACTIVE_HIGH | GPIO_PULL_DOWN)>  /* ROW0 */
            , <&xiao_d 7 (GPIO_ACTIVE_HIGH | GPIO_PULL_DOWN)>  /* ROW1 */
            , <&xiao_d 8 (GPIO_ACTIVE_HIGH | GPIO_PULL_DOWN)>  /* ROW2 */
            , <&xiao_d 9 (GPIO_ACTIVE_HIGH | GPIO_PULL_DOWN)>  /* ROW3 */
            ;
    };
};

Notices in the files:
parts and their libraries:
Derived from dennisleexyz/libmodulo SW_PG1316M (GPL-3.0); this file is GPL-3.0.
